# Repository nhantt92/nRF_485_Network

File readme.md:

# develope RS485-Network and nRF-Network

## HW design

### Relay Node

### Sensor Node

### Master

## FW

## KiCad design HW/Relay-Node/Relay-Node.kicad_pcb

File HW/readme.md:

# Harware 485 and nRF Network

## Relay Node

## Sensor Node

## Master Node

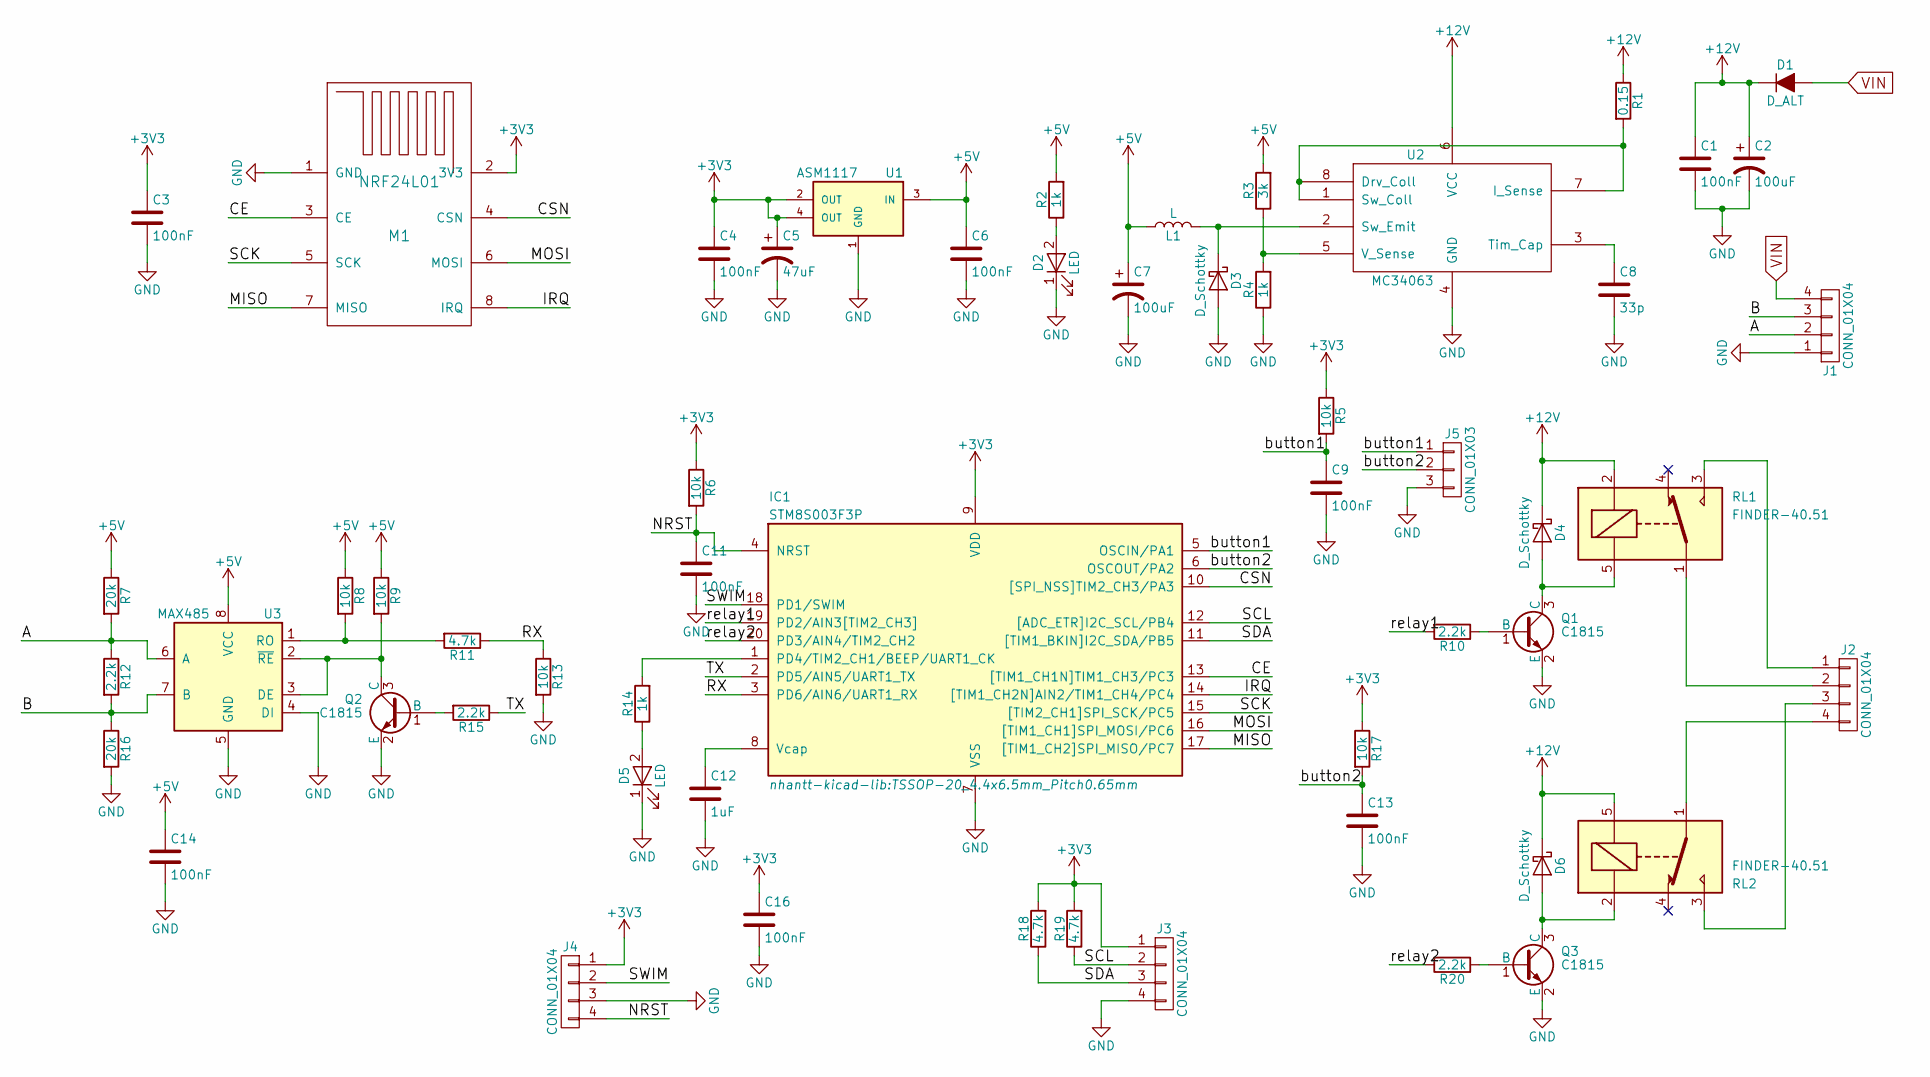
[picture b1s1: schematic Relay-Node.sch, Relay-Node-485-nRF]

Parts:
C1, C3, C4, C6, C9, C11, C13, C14, C16: 100nF; C_0805_HandSoldering
C2: 100uF; CP_Elec_8x10.5
C5: 47uF; CP_Tantalum_Case-C_EIA-6032-28_Reflow
C7: 100uF; CP_Elec_8x10
C8: 33p; C_0805_HandSoldering
C12: 1uF; C_0805_HandSoldering
D1: D_ALT; D_SMA_Standard
D2, D5: LED; LED_0805
D3: D_Schottky; D_SMB_Handsoldering
D4, D6: D_Schottky; D_SMA_Standard
IC1: STM8S003F3P; TSSOP-20_4.4x6.5mm_Pitch0.65mm
J1, J2: CONN_01X04; Domino-5.08mm_4pol
J3: CONN_01X04; Header-4pin-2.54
J4: CONN_01X04; Pin_Header_Straight_1x04_Pitch2.54mm
J5: CONN_01X03; Header-3pin-2.54
L1: L; Inductor_5.2x5.8x4.5
M1: NRF24L01
Q1, Q2, Q3: C1815; SOT-23
R1: 0.15; R_1206_HandSoldering
R2, R4, R14: 1k; R_0805_HandSoldering
R3: 3k; R_0805_HandSoldering
R5, R6, R8, R9, R13, R17: 10k; R_0805_HandSoldering
R7, R16: 20k; R_0805_HandSoldering
R10, R12, R15, R20: 2.2k; R_0805_HandSoldering
R11, R18, R19: 4.7k; R_0805_HandSoldering
RL1, RL2: FINDER-40.51; Relay_SRD-SONGLE
U1: ASM1117; SOT-223
U2: MC34063; SOIC-8_3.9x4.9mm_Pitch1.27mm
U3: MAX485; SOIC-8_3.9x4.9mm_Pitch1.27mm

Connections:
+3V3: C3.1, C4.1, C5.1, C16.1, IC1.9 (VDD), J3.1, J4.1, M1.2 (3V3), R5.1, R6.1, R17.1, R18.2, R19.2, U1.2 (OUT), U1.4 (OUT)
+5V: C6.1, C7.1, C14.1, L1.1, R2.2, R3.2, R7.1, R8.1, R9.1, U1.3 (IN), U3.8 (VCC)
+12V: C1.1, C2.1, D1.1 (K), D4.1 (K), D6.1 (K), R1.1, RL1.2, RL2.5, U2.6 (VCC)
/A: J1.2, R7.2, R12.1, U3.6 (A)
/B: J1.3, R12.2, R16.1, U3.7 (B)
/CE: IC1.13 ([TIM1_CH1N]TIM1_CH3/PC3), M1.3 (CE)
/CSN: IC1.10 ([SPI_NSS]TIM2_CH3/PA3), M1.4 (CSN)
/IRQ: IC1.14 ([TIM1_CH2N]AIN2/TIM1_CH4/PC4), M1.8 (IRQ)
/MISO: IC1.17 ([TIM1_CH2]SPI_MISO/PC7), M1.7 (MISO)
/MOSI: IC1.16 ([TIM1_CH1]SPI_MOSI/PC6), M1.6 (MOSI)
/NRST: C11.1, IC1.4 (NRST), J4.4, R6.2
/RX: IC1.3 (PD6/AIN6/UART1_RX), R11.1, R13.1
/SCK: IC1.15 ([TIM2_CH1]SPI_SCK/PC5), M1.5 (SCK)
/SCL: IC1.12 ([ADC_ETR]I2C_SCL/PB4), J3.2, R19.1
/SDA: IC1.11 ([TIM1_BKIN]I2C_SDA/PB5), J3.3, R18.1
/SWIM: IC1.18 (PD1/SWIM), J4.2
/TX: IC1.2 (PD5/AIN5/UART1_TX), R15.1
/button1: C9.1, IC1.5 (OSCIN/PA1), J5.1, R5.2
/button2: C13.1, IC1.6 (OSCOUT/PA2), J5.2, R17.2
/relay1: IC1.19 (PD2/AIN3[TIM2_CH3]), R10.2
/relay2: IC1.20 (PD3/AIN4/TIM2_CH2), R20.2
GND: C1.2, C2.2, C3.2, C4.2, C5.2, C6.2, C7.2, C8.2, C9.2, C11.2, C12.2, C13.2, C14.2, C16.2, D2.1 (K), D3.2 (A), D5.1 (K), IC1.7 (VSS), J1.1, J3.4, J4.3, J5.3, M1.1 (GND), Q1.2 (E), Q2.2 (E), Q3.2 (E), R4.1, R13.2, R16.2, U1.1 (GND), U2.4 (GND), U3.4 (DI), U3.5 (GND)
unnamed: C8.1, U2.3 (Tim_Cap)
unnamed: C12.1, IC1.8 (Vcap)
unnamed: D2.2 (A), R2.1
unnamed: D3.1 (K), L1.2, U2.2 (Sw_Emit)
unnamed: D4.2 (A), Q1.3 (C), RL1.5
unnamed: D5.2 (A), R14.1
unnamed: D6.2 (A), Q3.3 (C), RL2.2
unnamed: IC1.1 (PD4/TIM2_CH1/BEEP/UART1_CK), R14.2
unnamed: J2.1, RL1.3
unnamed: J2.2, RL1.1
unnamed: J2.3, RL2.3
unnamed: J2.4, RL2.1
unnamed: Q1.1 (B), R10.1
unnamed: Q2.1 (B), R15.2
unnamed: Q2.3 (C), R9.2, U3.2 (~RE~), U3.3 (DE)
unnamed: Q3.1 (B), R20.1
unnamed: R1.2, U2.1 (Sw_Coll), U2.7 (I_Sense), U2.8 (Drv_Coll)
unnamed: R3.1, R4.2, U2.5 (V_Sense)
unnamed: R8.2, R11.2, U3.1 (RO)
VIN: D1.2 (A), J1.4

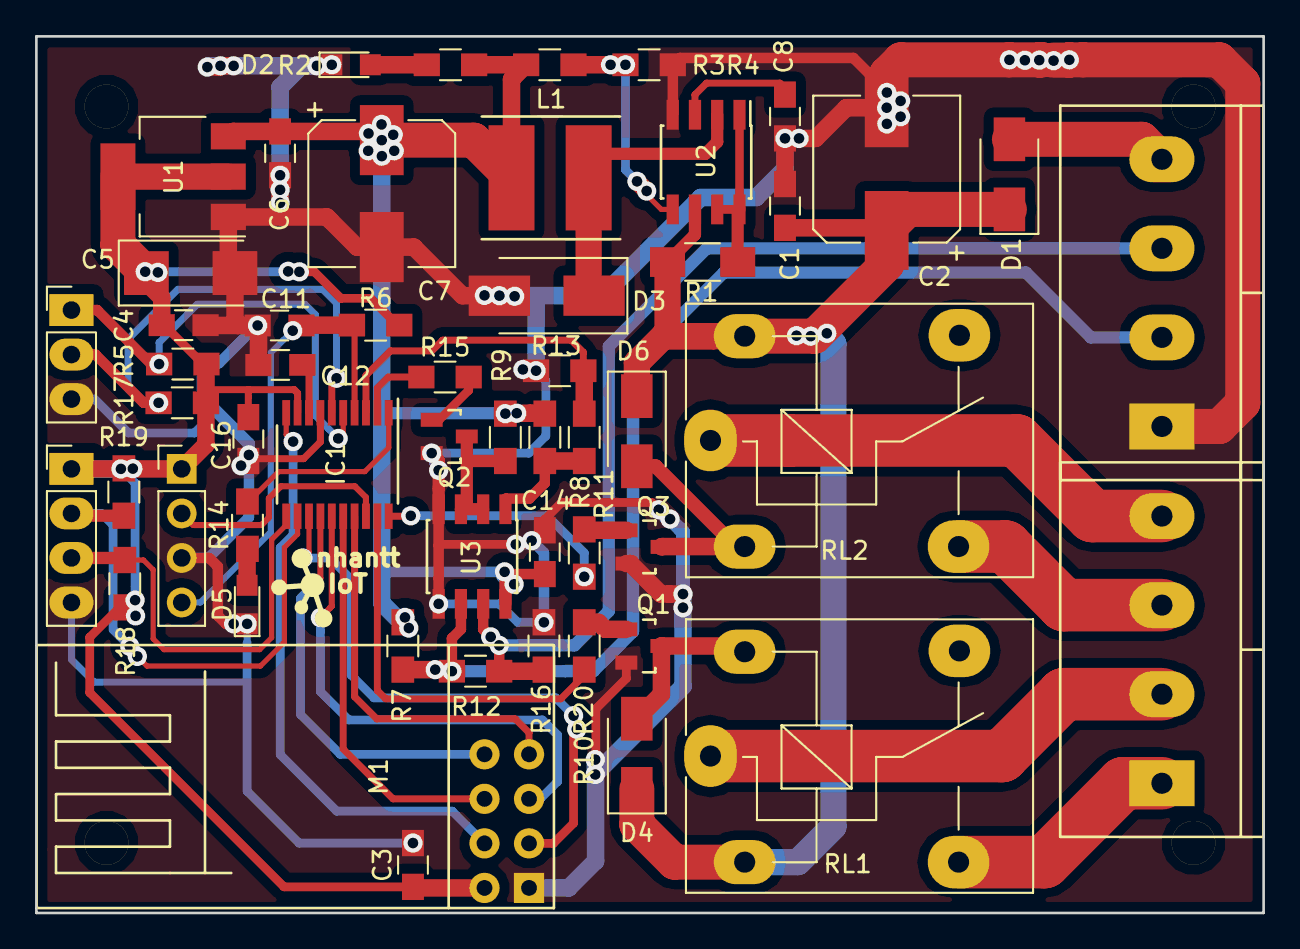
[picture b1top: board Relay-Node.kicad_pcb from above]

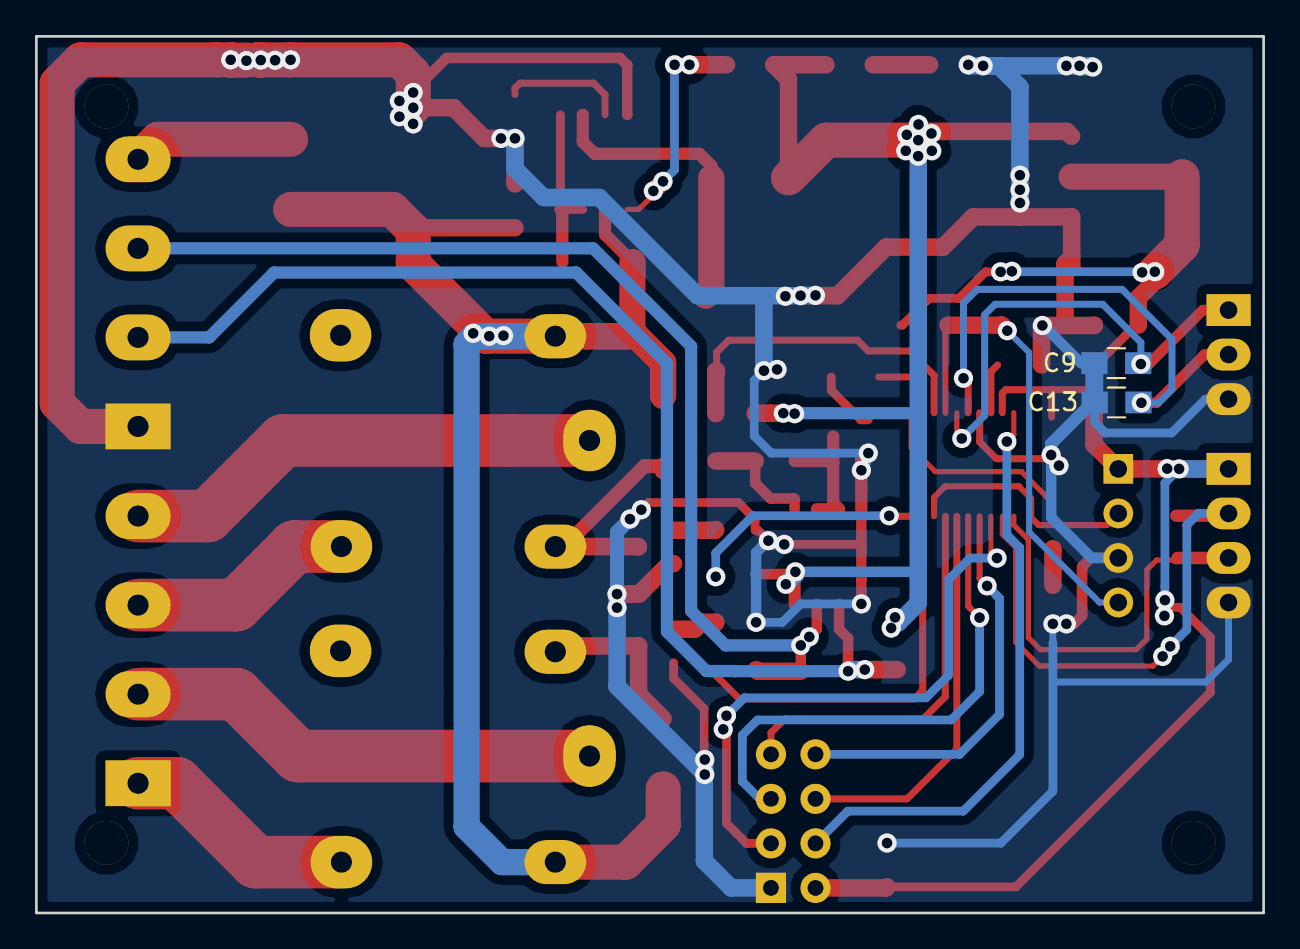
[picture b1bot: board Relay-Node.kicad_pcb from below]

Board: 2 copper layers, 70.0 x 50.0 mm, 56 parts (2 on the bottom side), 42 nets.

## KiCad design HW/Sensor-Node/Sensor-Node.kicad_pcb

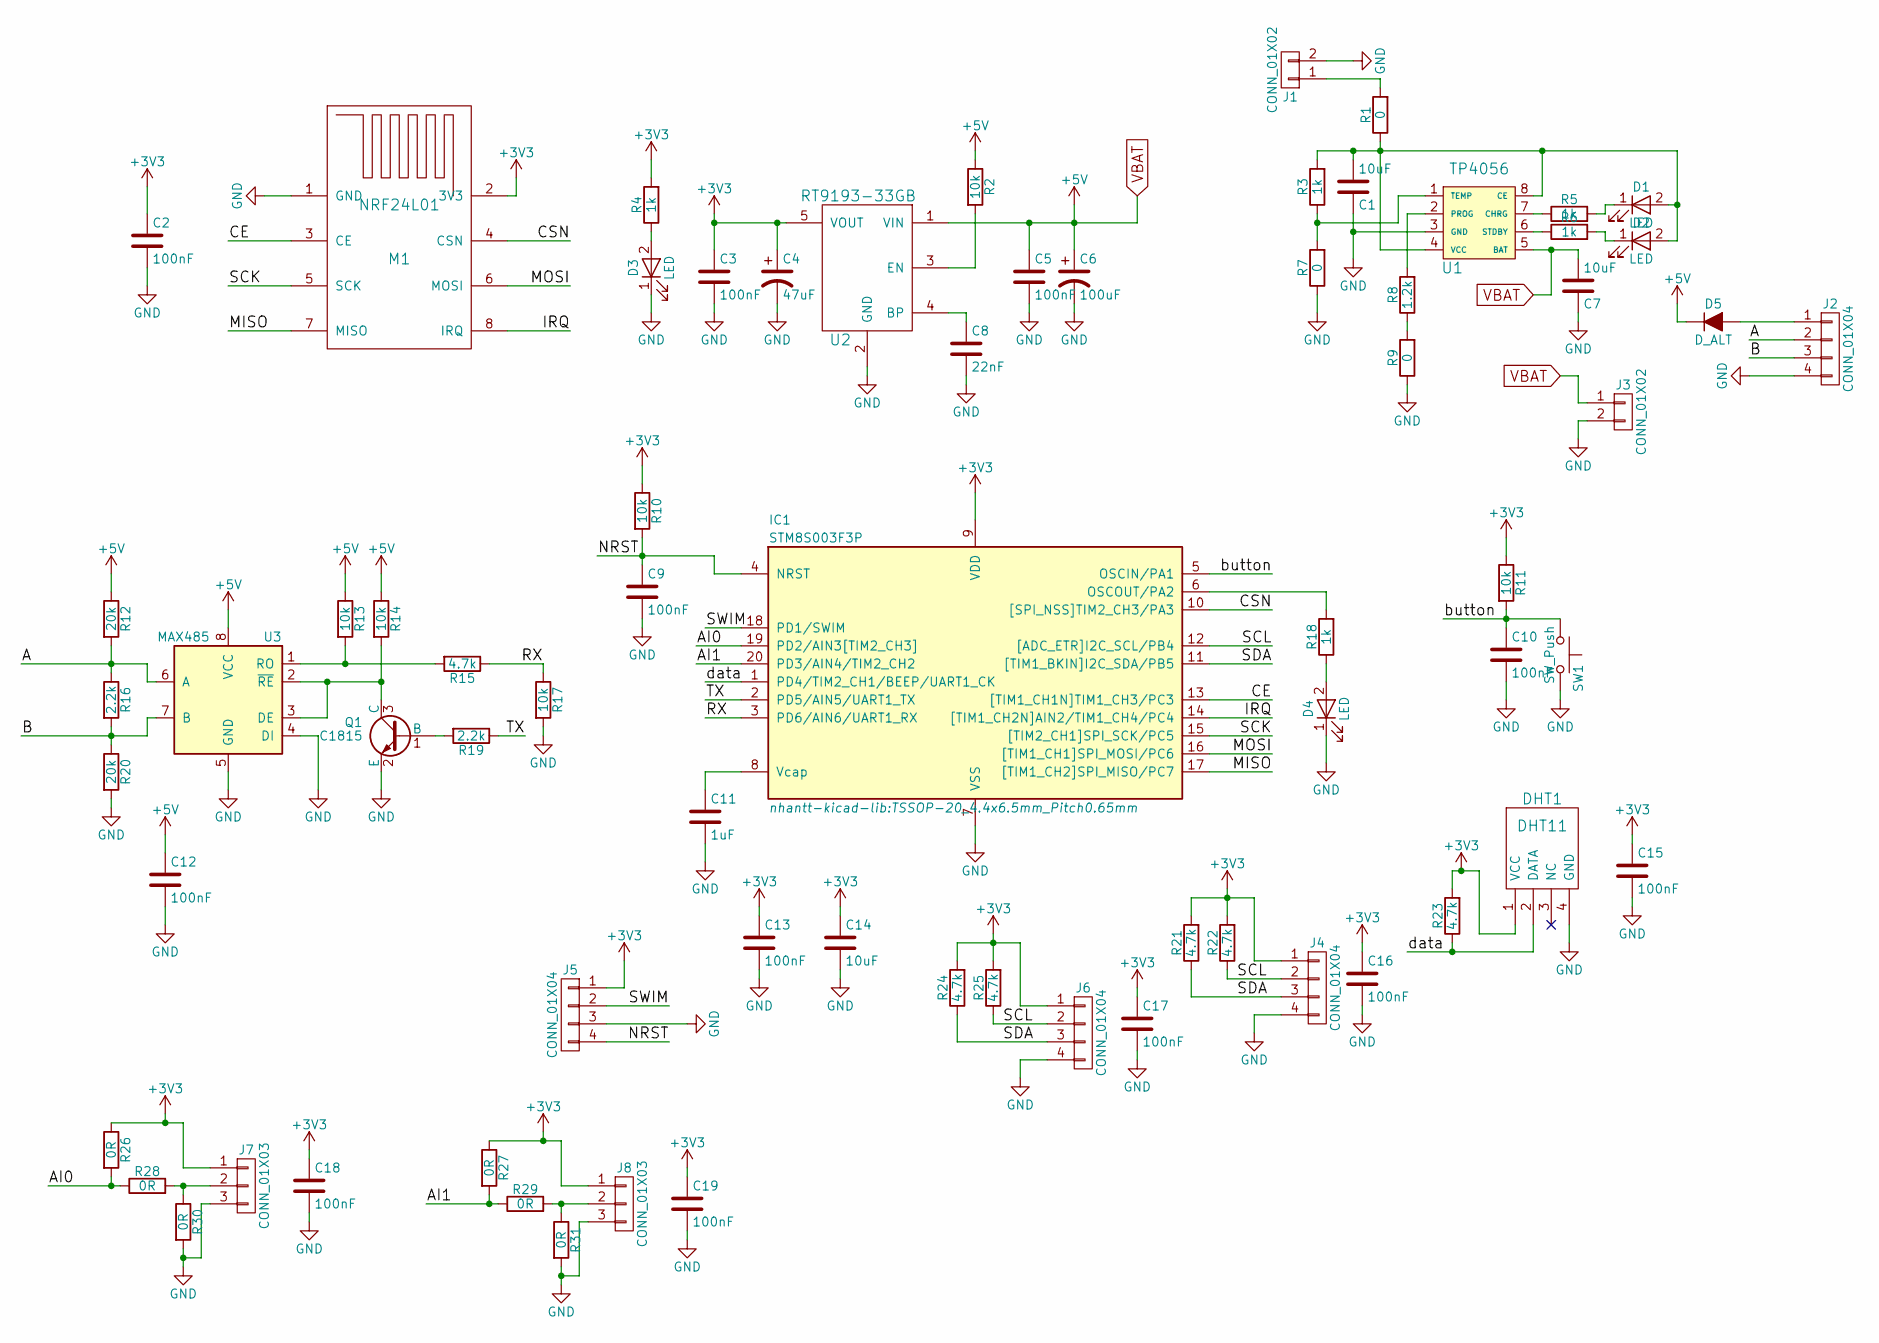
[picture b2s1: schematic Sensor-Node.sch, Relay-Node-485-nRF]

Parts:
C1, C7: 10uF; C_1206_HandSoldering
C2, C3, C5, C9, C10, C12, C13, C15, C16, C17, C18, C19: 100nF; C_0805_HandSoldering
C4: 47uF; C_1210_HandSoldering
C6: 100uF; C_1210_HandSoldering
C8: 22nF; C_0805_HandSoldering
C11: 1uF; C_0805_HandSoldering
C14: 10uF; R_1206_HandSoldering
D1, D2, D3, D4: LED; LED_0805_HandSoldering
D5: D_ALT; D_SMA_Standard
DHT1: DHT11
IC1: STM8S003F3P; TSSOP-20_4.4x6.5mm_Pitch0.65mm
J1, J3: CONN_01X02; Header-2pin-2.54-white
J2: CONN_01X04; Domino-5.08mm_4pol
J4, J5, J6: CONN_01X04; Header-4pin-2.54
J7, J8: CONN_01X03; Header-3pin-2.54
M1: NRF24L01; nRF24L01-Mini
Q1: C1815; SOT-23
R1, R7, R9: 0; R_0805_HandSoldering
R2, R10, R11, R13, R14, R17: 10k; R_0805_HandSoldering
R3, R4, R5, R6, R18: 1k; R_0805_HandSoldering
R8: 1.2k; R_0805_HandSoldering
R12, R20: 20k; R_0805_HandSoldering
R15, R21, R22, R23, R24, R25: 4.7k; R_0805_HandSoldering
R16, R19: 2.2k; R_0805_HandSoldering
R26, R27, R28, R29, R30, R31: 0R; R_0805_HandSoldering
SW1: SW_Push; SW_SPST_EVPBF
U1: TP4056; SOIC-8_3.9x4.9mm_Pitch1.27mm
U2: RT9193-33GB; SOT-23-5_HandSoldering
U3: MAX485; SOIC-8_3.9x4.9mm_Pitch1.27mm

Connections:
+3V3: C2.1, C3.1, C4.1, C13.1, C14.1, C15.1, C16.1, C17.1, C18.1, C19.1, DHT1.1 (VCC), IC1.9 (VDD), J4.1, J5.1, J6.1, J7.1, J8.1, M1.2 (3V3), R4.2, R10.1, R11.1, R21.2, R22.2, R23.2, R24.2, R25.2, R26.1, R27.1, U2.5 (VOUT)
/A: J2.2, R12.2, R16.1, U3.6 (A)
/AI0: IC1.19 (PD2/AIN3[TIM2_CH3]), R26.2, R28.1
/AI1: IC1.20 (PD3/AIN4/TIM2_CH2), R27.2, R29.1
/B: J2.3, R16.2, R20.1, U3.7 (B)
/CE: IC1.13 ([TIM1_CH1N]TIM1_CH3/PC3), M1.3 (CE)
/CSN: IC1.10 ([SPI_NSS]TIM2_CH3/PA3), M1.4 (CSN)
/IRQ: IC1.14 ([TIM1_CH2N]AIN2/TIM1_CH4/PC4), M1.8 (IRQ)
/MISO: IC1.17 ([TIM1_CH2]SPI_MISO/PC7), M1.7 (MISO)
/MOSI: IC1.16 ([TIM1_CH1]SPI_MOSI/PC6), M1.6 (MOSI)
/NRST: C9.1, IC1.4 (NRST), J5.4, R10.2
/RX: IC1.3 (PD6/AIN6/UART1_RX), R15.1, R17.1
/SCK: IC1.15 ([TIM2_CH1]SPI_SCK/PC5), M1.5 (SCK)
/SCL: IC1.12 ([ADC_ETR]I2C_SCL/PB4), J4.2, J6.2, R22.1, R25.1
/SDA: IC1.11 ([TIM1_BKIN]I2C_SDA/PB5), J4.3, J6.3, R21.1, R24.1
/SWIM: IC1.18 (PD1/SWIM), J5.2
/TX: IC1.2 (PD5/AIN5/UART1_TX), R19.1
/button: C10.1, IC1.5 (OSCIN/PA1), R11.2, SW1.1
/data: DHT1.2 (DATA), IC1.1 (PD4/TIM2_CH1/BEEP/UART1_CK), R23.1
GND: C1.1, C2.2, C3.2, C4.2, C5.2, C6.2, C7.1, C8.2, C9.2, C10.2, C11.2, C12.2, C13.2, C14.2, C15.2, C16.2, C17.2, C18.2, C19.2, D3.1 (K), D4.1 (K), DHT1.4 (GND), IC1.7 (VSS), J1.2, J2.4, J3.2, J4.4, J5.3, J6.4, J7.3, J8.3, M1.1 (GND), Q1.2 (E), R7.1, R9.1, R17.2, R20.2, R30.2, R31.2, SW1.2, U1.3 (GND), U2.2 (GND), U3.4 (DI), U3.5 (GND); also elsewhere on the board
unnamed: C1.2, D1.2 (A), D2.2 (A), R1.1, R3.2, U1.4 (VCC), U1.8 (CE)
unnamed: C8.1, U2.4 (BP)
unnamed: C11.1, IC1.8 (Vcap)
unnamed: D1.1 (K), R5.2
unnamed: D2.1 (K), R6.2
unnamed: D3.2 (A), R4.1
unnamed: D4.2 (A), R18.1
unnamed: D5.2 (A), J2.1
unnamed: IC1.6 (OSCOUT/PA2), R18.2
unnamed: J1.1, R1.2
unnamed: J7.2, R28.2, R30.1
unnamed: J8.2, R29.2, R31.1
unnamed: Q1.1 (B), R19.2
unnamed: Q1.3 (C), R14.2, U3.2 (~RE~), U3.3 (DE)
unnamed: R2.2, U2.3 (EN)
unnamed: R3.1, R7.2, U1.1 (TEMP)
unnamed: R5.1, U1.7 (CHRG)
unnamed: R6.1, U1.6 (STDBY)
unnamed: R8.1, R9.2
unnamed: R8.2, U1.2 (PROG)
unnamed: R13.2, R15.2, U3.1 (RO)
VBAT: C5.1, C6.1, C7.2, C12.1, D5.1 (K), J3.1, R2.1, R12.1, R13.1, R14.1, U1.5 (BAT), U2.1 (VIN), U3.8 (VCC); also elsewhere on the board

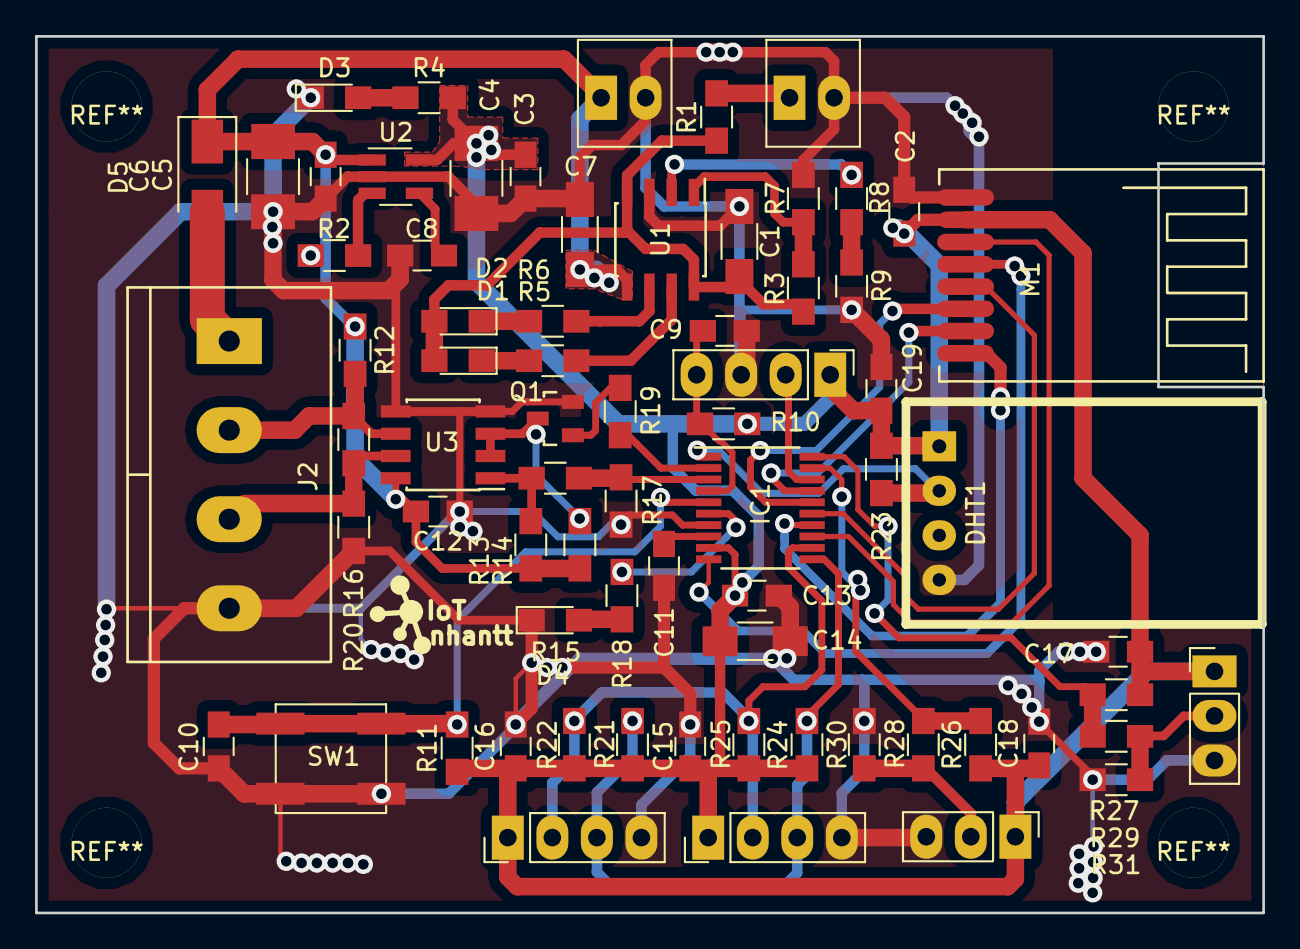
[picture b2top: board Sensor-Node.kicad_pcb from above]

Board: 2 copper layers, 70.0 x 50.0 mm, 71 parts (0 on the bottom side), 42 nets.

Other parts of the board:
BAT: CONN_01X02; Header-2pin-2.54-white

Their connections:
GND: BAT.2; also elsewhere on the board
VBAT: BAT.1; also elsewhere on the board

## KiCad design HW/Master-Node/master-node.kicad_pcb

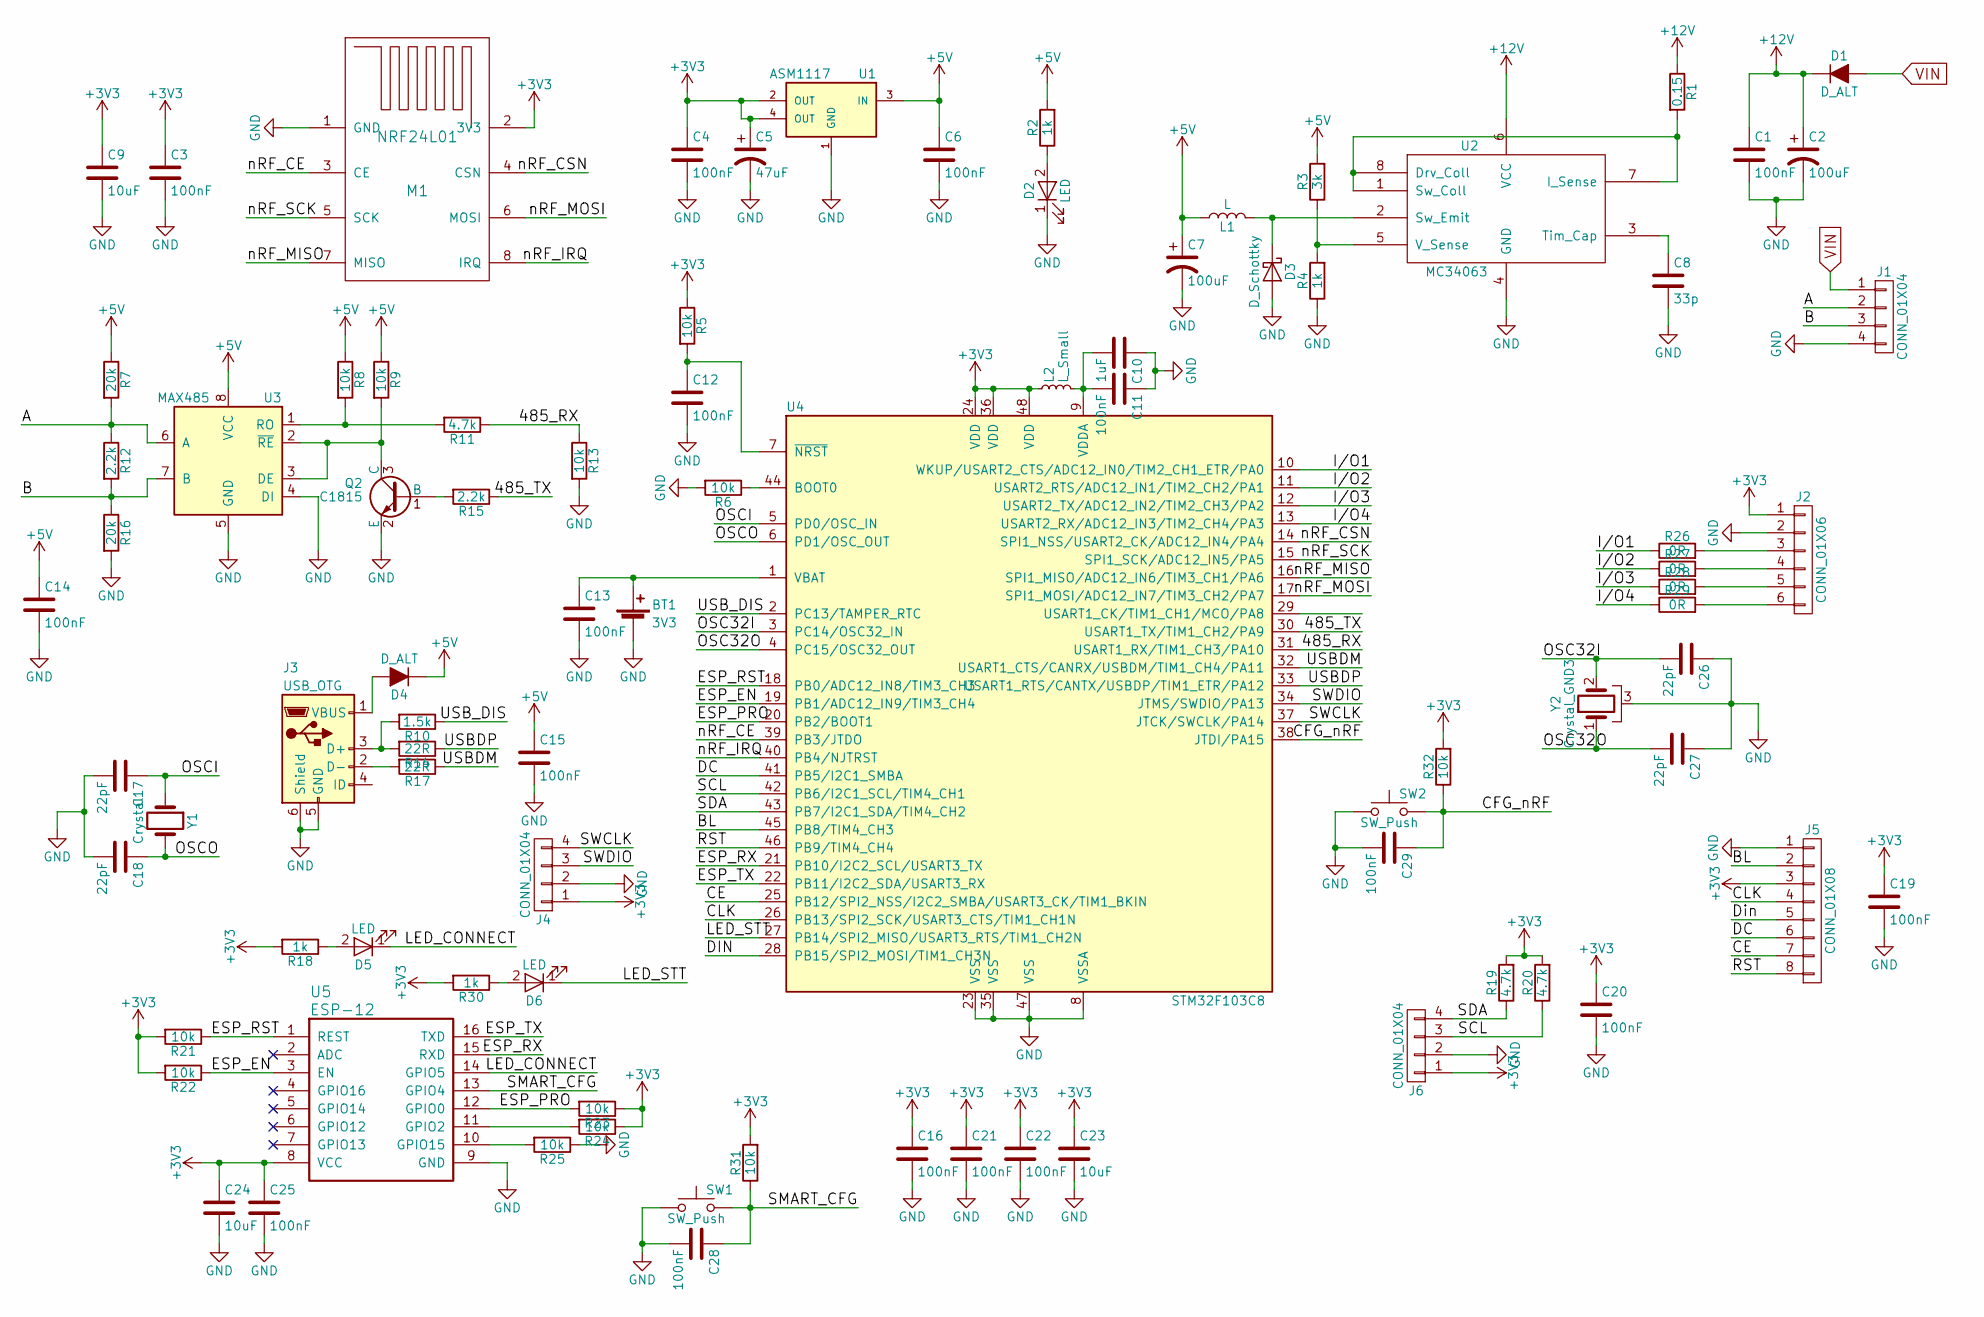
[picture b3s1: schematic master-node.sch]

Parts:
BT1: 3V3; BT3V3
C1, C3, C4, C6, C11, C12, C13, C14, C15, C16, C19, C20, C21, C22, C25, C28, C29: 100nF; C_0805_HandSoldering
C2: 100uF; CP_Elec_8x10.5
C5: 47uF; CP_Tantalum_Case-C_EIA-6032-28_Reflow
C7: 100uF; CP_Elec_8x10
C8: 33p; C_0805_HandSoldering
C9, C23, C24: 10uF; C_1206_HandSoldering
C10: 1uF; C_0805_HandSoldering
C17, C18, C26, C27: 22pF; C_0805_HandSoldering
D1: D_ALT; D_SMA_Standard
D2, D5, D6: LED; LED_0805
D3: D_Schottky; D_SMB_Handsoldering
D4: D_ALT; SOD-80
J1: CONN_01X04; Domino-5.08mm_4pol
J2: CONN_01X06; Header-6pin-2.54-white
J3: USB_OTG; USB_Micro-B
J4, J6: CONN_01X04; Header-4pin-2.54
J5: CONN_01X08; Pin_Header_Straight_1x08_Pitch2.54mm
L1: L; Inductor_5.2x5.8x4.5
L2: L_Small; R_0805_HandSoldering
M1: NRF24L01
Q2: C1815; SOT-23
R1: 0.15; R_1206_HandSoldering
R2, R4, R18, R30: 1k; R_0805_HandSoldering
R3: 3k; R_0805_HandSoldering
R5, R6, R8, R9, R13, R21, R22, R23, R24, R25, R31, R32: 10k; R_0805_HandSoldering
R7, R16: 20k; R_0805_HandSoldering
R10: 1.5k; R_0805_HandSoldering
R11, R19, R20: 4.7k; R_0805_HandSoldering
R12, R15: 2.2k; R_0805_HandSoldering
R14, R17: 22R; R_0805_HandSoldering
R26, R27, R28, R29: 0R; R_0805_HandSoldering
SW1, SW2: SW_Push; Button-6mm-smd
U1: ASM1117; SOT-223
U2: MC34063; SOIC-8_3.9x4.9mm_Pitch1.27mm
U3: MAX485; SOIC-8_3.9x4.9mm_Pitch1.27mm
U4: STM32F103C8; LQFP-48_7x7mm_Pitch0.5mm
U5: ESP-12; ESP-12E_SMD
Y1: Crystal; Crystal_SMD_HC49-SD
Y2: Crystal_GND3; Crystal_Round_Horizontal_3mm_smd

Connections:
+3V3: C3.1, C4.1, C5.1, C9.1, C16.1, C19.1, C20.1, C21.1, C22.1, C23.1, C24.1, C25.1, J2.1, J4.1, J5.3, J6.1, L2.1, M1.2 (3V3), R5.1, R18.2, R19.2, R20.2, R21.2, R22.2, R23.1, R24.1, R30.2, R31.2, R32.2, U1.2 (OUT), U1.4 (OUT), U4.24 (VDD), U4.36 (VDD), U4.48 (VDD), U5.8 (VCC)
+5V: C6.1, C7.1, C14.1, C15.1, D4.1 (K), L1.1, R2.2, R3.2, R7.1, R8.1, R9.1, U1.3 (IN), U3.8 (VCC)
+12V: C1.1, C2.1, D1.1 (K), R1.1, U2.6 (VCC)
/485_RX: R11.1, R13.1, U4.31 (USART1_RX/TIM1_CH3/PA10)
/485_TX: R15.1, U4.30 (USART1_TX/TIM1_CH2/PA9)
/A: J1.2, R7.2, R12.1, U3.6 (A)
/B: J1.3, R12.2, R16.1, U3.7 (B)
/BL: J5.2, U4.45 (PB8/TIM4_CH3)
/CE: J5.7, U4.25 (PB12/SPI2_NSS/I2C2_SMBA/USART3_CK/TIM1_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)
/CFG_nRF: C29.1, R32.1, SW2.2, U4.38 (JTDI/PA15); also elsewhere on the board
/CLK: J5.4, U4.26 (PB13/SPI2_SCK/USART3_CTS/TIM1_CH1N)
/DC: J5.6, U4.41 (PB5/I2C1_SMBA)
/DIN: J5.5, U4.28 (PB15/SPI2_MOSI/TIM1_CH3N)
/ESP_EN: R22.1, U4.19 (PB1/ADC12_IN9/TIM3_CH4), U5.3 (EN)
/ESP_PRO: R23.2, U4.20 (PB2/BOOT1), U5.12 (GPIO0)
/ESP_RST: R21.1, U4.18 (PB0/ADC12_IN8/TIM3_CH3), U5.1 (REST)
/ESP_RX: U4.21 (PB10/I2C2_SCL/USART3_TX), U5.15 (RXD)
/ESP_TX: U4.22 (PB11/I2C2_SDA/USART3_RX), U5.16 (TXD)
/I/O1: R26.1, U4.10 (WKUP/USART2_CTS/ADC12_IN0/TIM2_CH1_ETR/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)
/I/O2: R27.1, U4.11 (USART2_RTS/ADC12_IN1/TIM2_CH2/PA1)
/I/O3: R28.1, U4.12 (USART2_TX/ADC12_IN2/TIM2_CH3/PA2)
/I/O4: R29.1, U4.13 (USART2_RX/ADC12_IN3/TIM2_CH4/PA3)
/LED_CONNECT: D5.1 (K), U5.14 (GPIO5)
/LED_STT: D6.1 (K), U4.27 (PB14/SPI2_MISO/USART3_RTS/TIM1_CH2N)
/OSC32I: C26.2, U4.3 (PC14/OSC32_IN), Y2.2
/OSC32O: C27.2, U4.4 (PC15/OSC32_OUT), Y2.1
/OSCI: C17.1, U4.5 (PD0/OSC_IN), Y1.1
/OSCO: C18.1, U4.6 (PD1/OSC_OUT), Y1.2
/RST: J5.8, U4.46 (PB9/TIM4_CH4)
/SCL: J6.3, R20.1, U4.42 (PB6/I2C1_SCL/TIM4_CH1)
/SDA: J6.4, R19.1, U4.43 (PB7/I2C1_SDA/TIM4_CH2)
/SMART_CFG: C28.1, R31.1, SW1.2, U5.13 (GPIO4); also elsewhere on the board
/SWCLK: J4.4, U4.37 (JTCK/SWCLK/PA14)
/SWDIO: J4.3, U4.34 (JTMS/SWDIO/PA13)
/USBDM: R17.1, U4.32 (USART1_CTS/CANRX/USBDM/TIM1_CH4/PA11)
/USBDP: R14.1, U4.33 (USART1_RTS/CANTX/USBDP/TIM1_ETR/PA12)
/USB_DIS: R10.1, U4.2 (PC13/TAMPER_RTC)
/nRF_CE: M1.3 (CE), U4.39 (PB3/JTDO)
/nRF_CSN: M1.4 (CSN), U4.14 (SPI1_NSS/USART2_CK/ADC12_IN4/PA4)
/nRF_IRQ: M1.8 (IRQ), U4.40 (PB4/NJTRST)
/nRF_MISO: M1.7 (MISO), U4.16 (SPI1_MISO/ADC12_IN6/TIM3_CH1/PA6)
/nRF_MOSI: M1.6 (MOSI), U4.17 (SPI1_MOSI/ADC12_IN7/TIM3_CH2/PA7)
/nRF_SCK: M1.5 (SCK), U4.15 (SPI1_SCK/ADC12_IN5/PA5)
GND: BT1.2 (-), C1.2, C2.2, C3.2, C4.2, C5.2, C6.2, C7.2, C8.2, C9.2, C10.1, C11.1, C12.2, C13.2, C14.2, C15.2, C16.2, C17.2, C18.2, C19.2, C20.2, C21.2, C22.2, C23.2, C24.2, C25.2, C26.1, C27.1, C28.2, C29.2, D2.1 (K), D3.2 (A), J1.4, J2.2, J3.5 (GND), J3.6 (Shield), J4.2, J5.1, J6.2, M1.1 (GND), Q2.2 (E), R4.1, R6.2, R13.2, R16.2, R25.1, SW1.1, SW2.1, U1.1 (GND), U2.4 (GND), U3.4 (DI), U3.5 (GND), U4.8 (VSSA), U4.23 (VSS), U4.35 (VSS), U4.47 (VSS), U5.9 (GND), Y2.3; also elsewhere on the board
unnamed: BT1.1 (+), C13.1, U4.1 (VBAT)
unnamed: C8.1, U2.3 (Tim_Cap)
unnamed: C10.2, C11.2, L2.2, U4.9 (VDDA)
unnamed: C12.1, R5.2, U4.7 (~NRST)
unnamed: D2.2 (A), R2.1
unnamed: D3.1 (K), L1.2, U2.2 (Sw_Emit)
unnamed: D4.2 (A), J3.1 (VBUS)
unnamed: D5.2 (A), R18.1
unnamed: D6.2 (A), R30.1
unnamed: J2.3, R26.2
unnamed: J2.4, R27.2
unnamed: J2.5, R28.2
unnamed: J2.6, R29.2
unnamed: J3.2 (D-), R17.2
unnamed: J3.3 (D+), R10.2, R14.2
unnamed: Q2.1 (B), R15.2
unnamed: Q2.3 (C), R9.2, U3.2 (~RE~), U3.3 (DE)
unnamed: R1.2, U2.1 (Sw_Coll), U2.7 (I_Sense), U2.8 (Drv_Coll)
unnamed: R3.1, R4.2, U2.5 (V_Sense)
unnamed: R6.1, U4.44 (BOOT0)
unnamed: R8.2, R11.2, U3.1 (RO)
unnamed: R24.2, U5.11 (GPIO2)
unnamed: R25.2, U5.10 (GPIO15)
VIN: D1.2 (A), J1.1

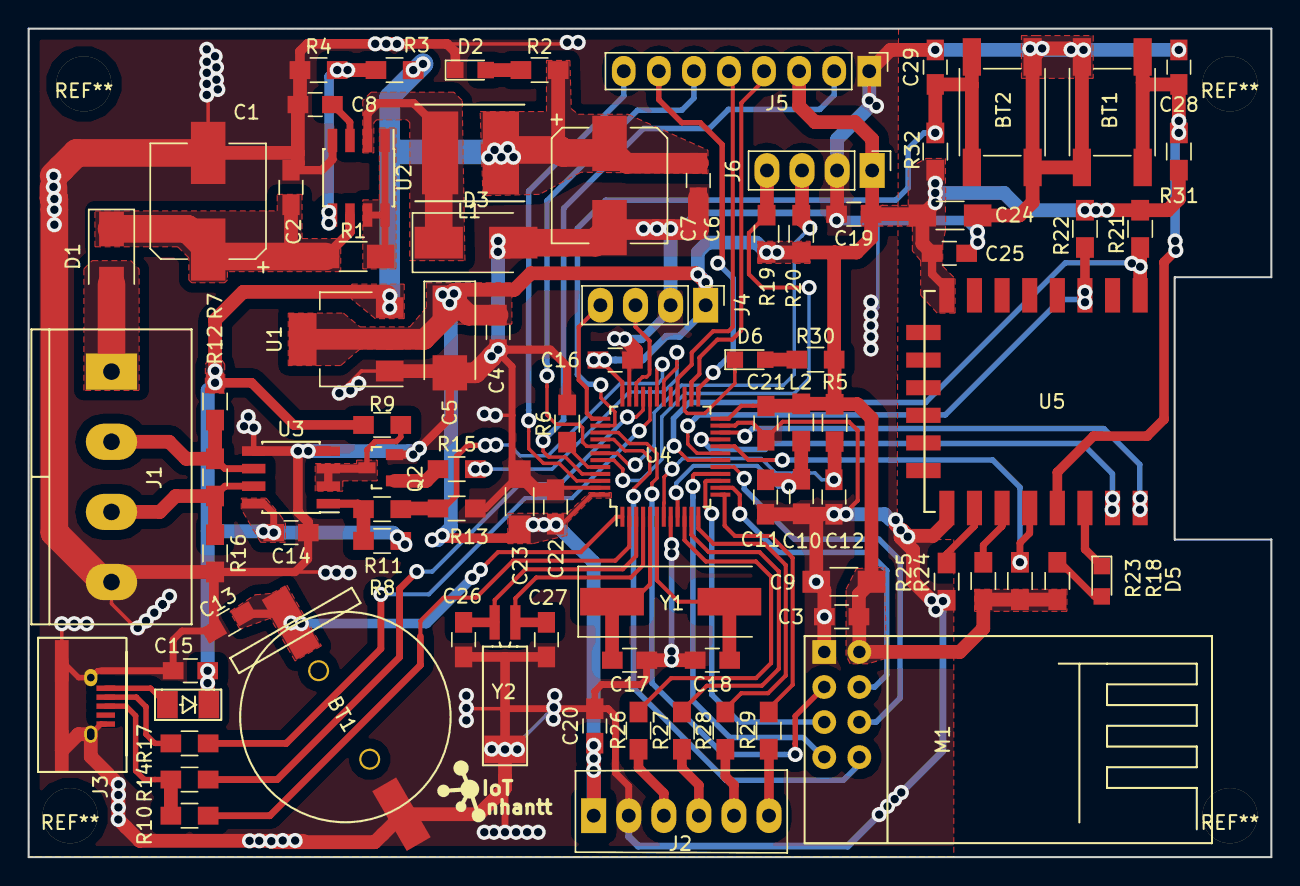
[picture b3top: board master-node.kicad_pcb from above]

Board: 2 copper layers, 90.0 x 60.0 mm, 87 parts (0 on the bottom side), 68 nets.

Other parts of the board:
BT1#2, BT2: SW_Push; Button-6mm-smd

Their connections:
/CFG_nRF: BT2.2; also elsewhere on the board
/SMART_CFG: BT1#2.2; also elsewhere on the board
GND: BT1#2.1, BT2.1; also elsewhere on the board

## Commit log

2017-11-07 init project with schematic
2017-11-07 add cover on pcb
2017-12-15 layout pcb relay-node
2017-12-15 add vit-hole
2017-12-16 complete layout pcb relay-node
2017-12-17 add readme
2017-12-17 fix readme
2017-12-30 complete sensor-node
2018-01-02 add schematic master-node
2018-01-03 add footprint component
2018-01-08 upload layout
2018-01-09 complete layout master node
2018-01-12 modified label
